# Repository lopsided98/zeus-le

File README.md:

# zeus-le

### Synchronized wireless audio recording system

zeus-le is a system to allow a set of wireless digital audio recorders to maintain sub-sample accurate time synchronization over indefinite periods. A central node broadcasts periodic synchronization packets over Bluetooth LE, which are received by an arbitrary number of recording nodes. The recording nodes use a digital phase-locked loop (PLL) to keep the audio sample clock in sync with the reference. The PLL is implemented using a Kalman filter and linear quadratic regulator.

This repository contains both firmware source code and a custom PCB design for the audio recording hardware. The firmware is written in C for a Nordic nRF53 running Zephyr RTOS. The PCB is designed in KiCad and hosts an nRF53+nRF7002 module, battery charger, SD card, audio ADC and voltage regulators.

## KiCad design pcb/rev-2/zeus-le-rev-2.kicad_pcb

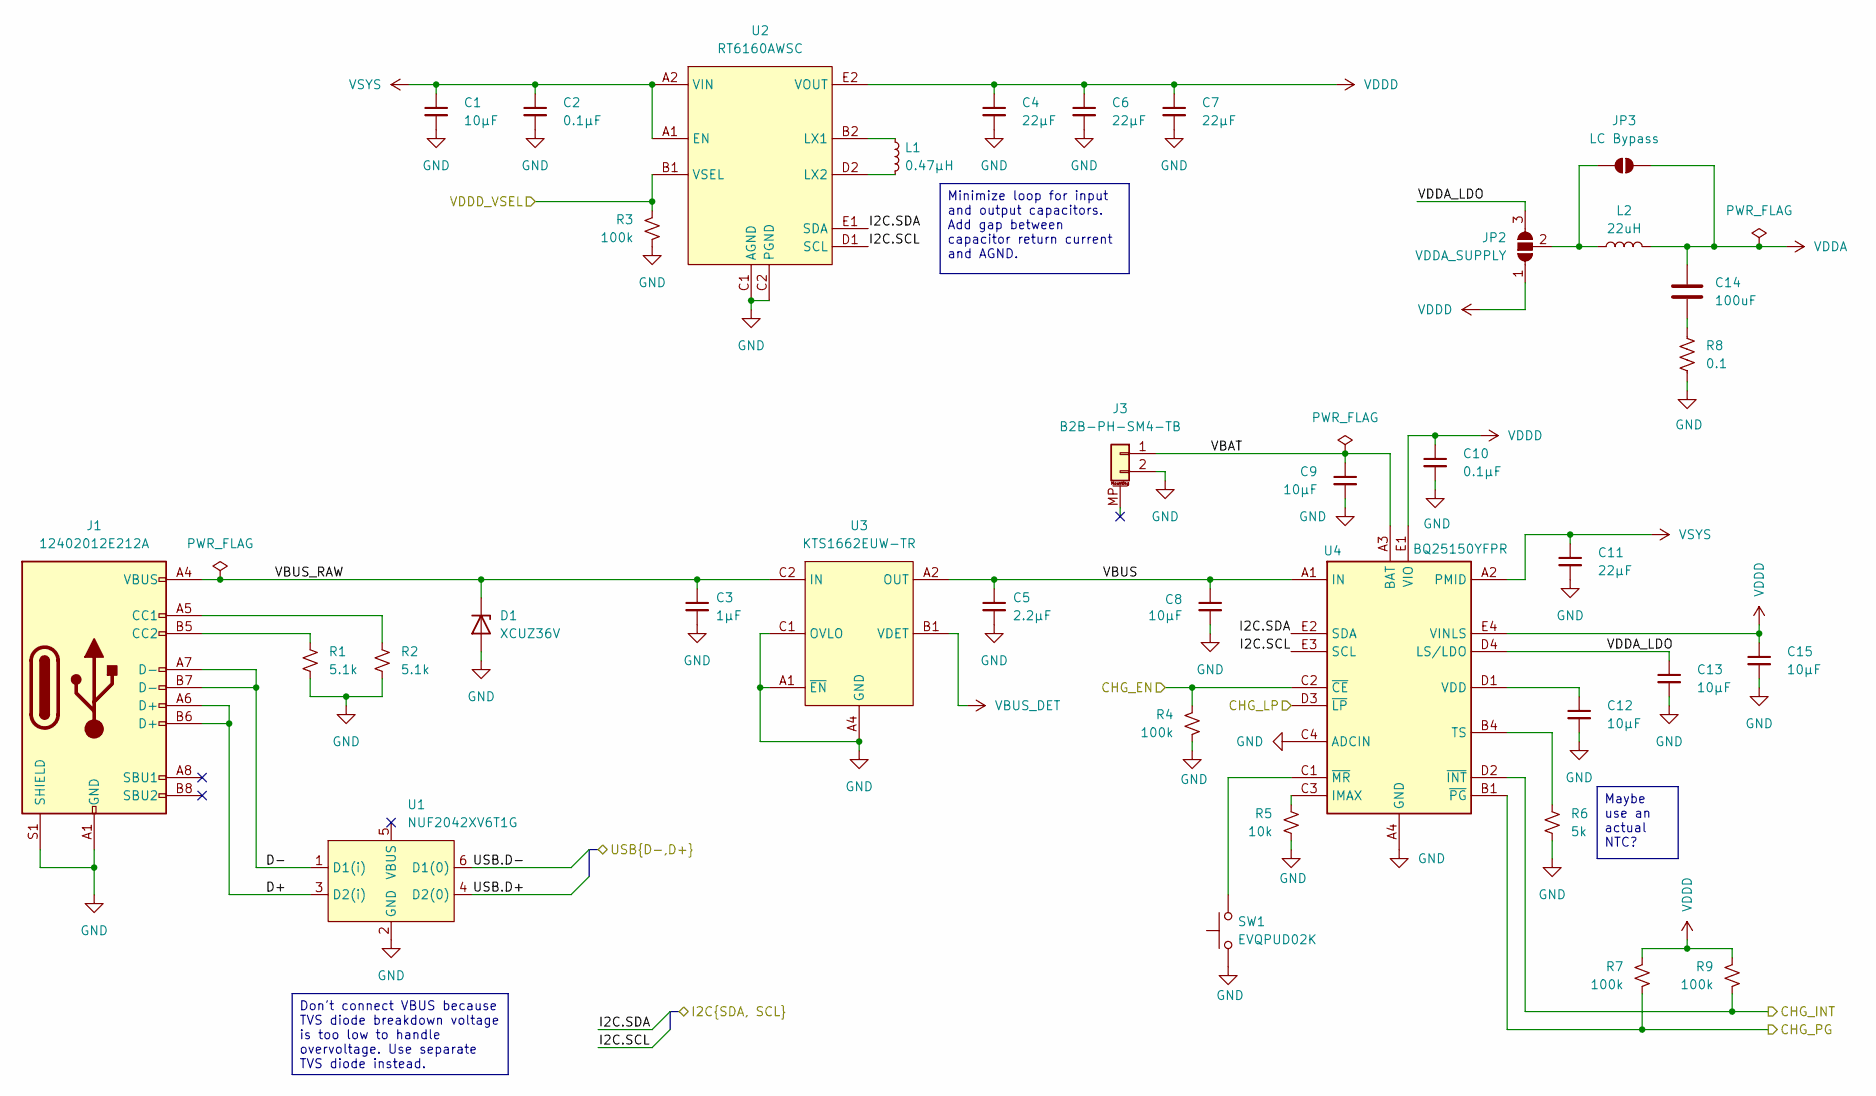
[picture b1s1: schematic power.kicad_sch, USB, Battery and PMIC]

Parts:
C1: 10µF; C_0603_1608Metric
C2, C10: 0.1µF; C_0402_1005Metric_Silkscreen_Clearance
C3: 1µF; C_0603_1608Metric
C4, C6, C7, C11: 22µF; C_0603_1608Metric
C5: 2.2µF; C_0402_1005Metric_Silkscreen_Clearance
C8, C9, C12, C13, C15: 10µF; C_0402_1005Metric_Silkscreen_Clearance
C14: 100uF; C_1206_3216Metric
D1: XCUZ36V; D_SOD-323
J1: 12402012E212A; USB_C_Receptacle_Amphenol_12402012E21-2A
J3: B2B-PH-SM4-TB; JST_PH_B2B-PH-SM4-TB_1x02-1MP_P2.00mm_Vertical; mouser# 306-B2BPHSM4TBLFSN
JP2: VDDA_SUPPLY; SolderJumper-3_P2.0mm_Open_TrianglePad1.0x1.5mm
JP3: LC Bypass; SolderJumper-2_P1.3mm_Open_TrianglePad1.0x1.5mm
L1: 0.47µH; L_Bourns_SRP4020FA_4.1x4.1mm
L2: 22uH; L_0805_2012Metric
R1, R2: 5.1k; R_0402_1005Metric_Silkscreen_Clearance
R3, R4, R7, R9: 100k; R_0402_1005Metric_Silkscreen_Clearance
R5: 10k; R_0402_1005Metric_Silkscreen_Clearance
R6: 5k; R_0402_1005Metric_Silkscreen_Clearance
R8: 0.1; R_0603_1608Metric
SW1: EVQPUD02K; Panasonic_EVQPUM_EVQPUD
U1: NUF2042XV6T1G; SOT-563
U2: RT6160AWSC; Richtek_WLCSP-15_1.4x2.3mm_Layout3x5_P0.4mm_NSMD
U3: KTS1662EUW-TR; Kinetic_WLCSP-12_1.94x1.28mm_Layout4x3_P0.4mm_Ball0.25mm_Pa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
U4: BQ25150YFPR; Texas_DSBGA-20_1.615x2.015mm_Layout4x5_P0.4mm_NSMD

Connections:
/Audio/I2C.SCL: U2.D1 (SCL), U4.E3 (SCL); also elsewhere on the board
/Audio/I2C.SDA: U2.E1 (SDA), U4.E2 (SDA); also elsewhere on the board
/MCU/CHG_EN: R4.1, U4.C2 (~CE); also elsewhere on the board
/MCU/CHG_INT: R9.2, U4.D2 (~INT); also elsewhere on the board
/MCU/CHG_LP: U4.D3 (~LP); also elsewhere on the board
/MCU/CHG_PG: R7.2, U4.B1 (~PG); also elsewhere on the board
/MCU/USB.D+: U1.4 (D2(0)); also elsewhere on the board
/MCU/USB.D-: U1.6 (D1(0)); also elsewhere on the board
/MCU/VDDD_VSEL: R3.1, U2.B1 (VSEL); also elsewhere on the board
/Power/D+: J1.A6 (D+), J1.B6 (D+), U1.3 (D2(i))
/Power/D-: J1.A7 (D-), J1.B7 (D-), U1.1 (D1(i))
/Power/VBAT: C9.1, J3.1, U4.A3 (BAT), U4.B3 (BAT)
/Power/VBUS: C5.1, C8.1, U3.A2 (OUT), U3.A3 (OUT), U3.B2 (OUT), U4.A1 (IN)
/Power/VBUS_RAW: C3.1, D1.1 (K), J1.A4 (VBUS), J1.A9 (VBUS), J1.B4 (VBUS), J1.B9 (VBUS), U3.B3 (IN), U3.C2 (IN), U3.C3 (IN)
/Power/VDDA_LDO: C13.1, JP2.3 (B), U4.D4 (LS/LDO)
GND: C1.2, C2.2, C3.2, C4.2, C5.2, C6.2, C7.2, C8.2, C9.2, C10.2, C11.2, C12.2, C13.2, C15.2, D1.2 (A), J1.A1 (GND), J1.A12 (GND), J1.B1 (GND), J1.B12 (GND), J1.S1 (SHIELD), J3.2, R1.2, R2.2, R3.2, R4.2, R5.2, R6.2, R8.2, SW1.1, U1.2 (GND), U2.C1 (AGND), U2.C2 (PGND), U2.C3 (PGND), U3.A1 (~EN), U3.A4 (GND), U3.B4 (GND), U3.C1 (OVLO), U3.C4 (GND), U4.A4 (GND), U4.C4 (ADCIN); also elsewhere on the board
unnamed: C14.2, R8.1
unnamed: J1.A5 (CC1), R2.1
unnamed: J1.B5 (CC2), R1.1
unnamed: JP2.2 (C), JP3.1 (A), L2.1
unnamed: L1.1, U2.B2 (LX1), U2.B3 (LX1)
unnamed: L1.2, U2.D2 (LX2), U2.D3 (LX2)
unnamed: R5.1, U4.C3 (IMAX)
unnamed: R6.1, U4.B4 (TS)
unnamed: C12.1, U4.D1 (VDD)
unnamed: SW1.2, U4.C1 (~MR)
VBUS_DET: U3.B1 (VDET); also elsewhere on the board
VDDA: C14.1, JP3.2 (B), L2.2; also elsewhere on the board
VDDD: C4.1, C6.1, C7.1, C10.1, C15.1, JP2.1 (A), R7.1, R9.1, U2.E2 (VOUT), U2.E3 (VOUT), U4.E1 (VIO), U4.E4 (VINLS); also elsewhere on the board
VSYS: C1.1, C2.1, C11.1, U2.A1 (EN), U2.A2 (VIN), U2.A3 (VIN), U4.A2 (PMID), U4.B2 (PMID)

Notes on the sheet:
Minimize loop for input and output capacitors. Add gap between capacitor return current and AGND.
Don't connect VBUS because TVS diode breakdown voltage is too low to handle overvoltage. Use separate TVS diode instead.
Maybe use an actual NTC?

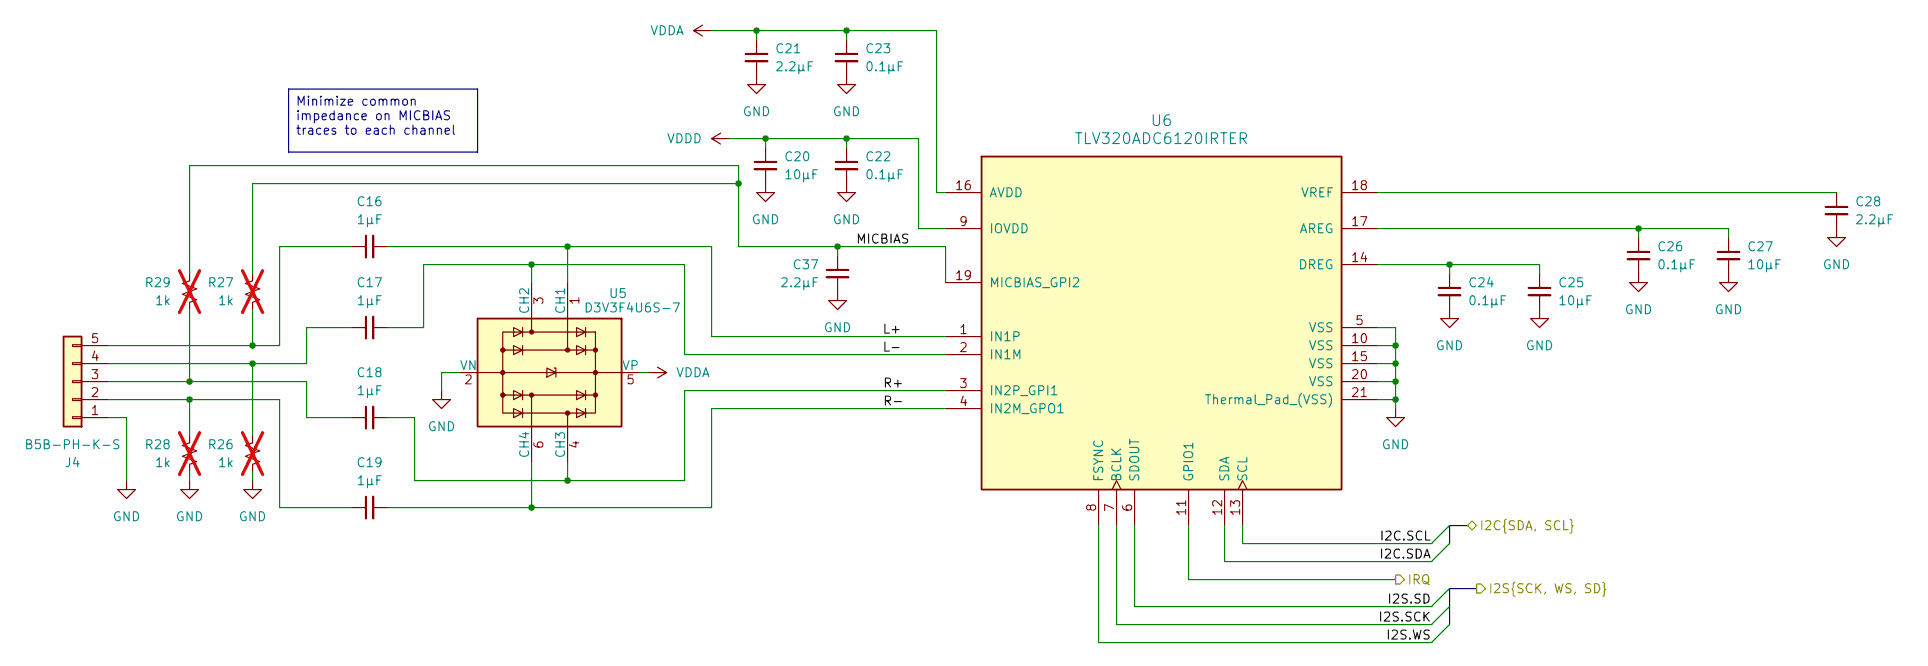
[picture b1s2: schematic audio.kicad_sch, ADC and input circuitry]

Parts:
C16, C17, C18, C19: 1µF; C_1206_3216Metric
C20, C25, C27: 10µF; C_0603_1608Metric
C21, C28, C37: 2.2µF; C_0402_1005Metric_Silkscreen_Clearance
C22, C23, C24, C26: 0.1µF; C_0402_1005Metric_Silkscreen_Clearance
J4: B5B-PH-K-S; JST_PH_B5B-PH-K_1x05_P2.00mm_Vertical
R26, R27, R28, R29: 1k; R_0402_1005Metric_Silkscreen_Clearance; not fitted
U5: D3V3F4U6S-7; SOT-363_SC-70-6
U6: TLV320ADC6120IRTER; Texas_RTE_WQFN-20-1EP_3x3mm_P0.5mm_EP1.4x1.4mm_ThermalVias

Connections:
/Audio/I2C.SCL: U6.13 (SCL); also elsewhere on the board
/Audio/I2C.SDA: U6.12 (SDA); also elsewhere on the board
/Audio/I2S.SCK: U6.7 (BCLK); also elsewhere on the board
/Audio/I2S.SD: U6.6 (SDOUT); also elsewhere on the board
/Audio/I2S.WS: U6.8 (FSYNC); also elsewhere on the board
/Audio/IRQ: U6.11 (GPIO1); also elsewhere on the board
/Audio/L+: C16.2, U5.1 (CH1), U6.1 (IN1P)
/Audio/L-: C17.2, U5.3 (CH2), U6.2 (IN1M)
/Audio/MICBIAS: C37.1, R27.1, R29.1, U6.19 (MICBIAS_GPI2)
/Audio/R+: C18.2, U5.4 (CH3), U6.3 (IN2P_GPI1)
/Audio/R-: C19.2, U5.6 (CH4), U6.4 (IN2M_GPO1)
GND: C20.2, C21.2, C22.2, C23.2, C24.2, C25.2, C26.2, C27.2, C28.2, C37.2, J4.1, R26.2, R28.2, U5.2 (VN), U6.5 (VSS), U6.10 (VSS), U6.15 (VSS), U6.20 (VSS), U6.21 (Thermal_Pad_(VSS)); also elsewhere on the board
unnamed: C19.1, J4.2, R28.1
unnamed: C18.1, J4.3, R29.2
unnamed: C17.1, J4.4, R26.1
unnamed: C16.1, J4.5, R27.2
unnamed: C26.1, C27.1, U6.17 (AREG)
unnamed: C24.1, C25.1, U6.14 (DREG)
unnamed: C28.1, U6.18 (VREF)
VDDA: C21.1, C23.1, U5.5 (VP), U6.16 (AVDD); also elsewhere on the board
VDDD: C20.1, C22.1, U6.9 (IOVDD); also elsewhere on the board

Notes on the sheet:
Minimize common impedance on MICBIAS traces to each channel

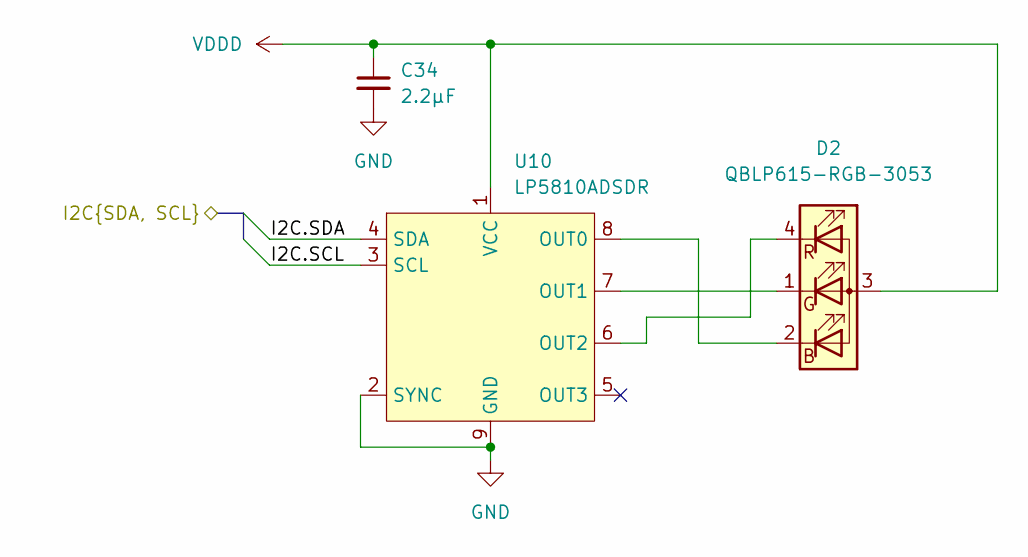
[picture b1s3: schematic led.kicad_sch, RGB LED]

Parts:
C34: 2.2µF; C_0402_1005Metric_Silkscreen_Clearance
D2: QBLP615-RGB-3053; LED_QBLP615-RGB-3053
U10: LP5810ADSDR; WSON-8-1EP_3x3mm_P0.65mm_EP1.65x2.4mm_ThermalVias

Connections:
/Audio/I2C.SCL: U10.3 (SCL); also elsewhere on the board
/Audio/I2C.SDA: U10.4 (SDA); also elsewhere on the board
GND: C34.2, U10.2 (SYNC), U10.9 (GND); also elsewhere on the board
unnamed: D2.2 (BK), U10.8 (OUT0)
unnamed: D2.1 (GK), U10.7 (OUT1)
unnamed: D2.4 (RK), U10.6 (OUT2)
VDDD: C34.1, D2.3 (A), U10.1 (VCC); also elsewhere on the board

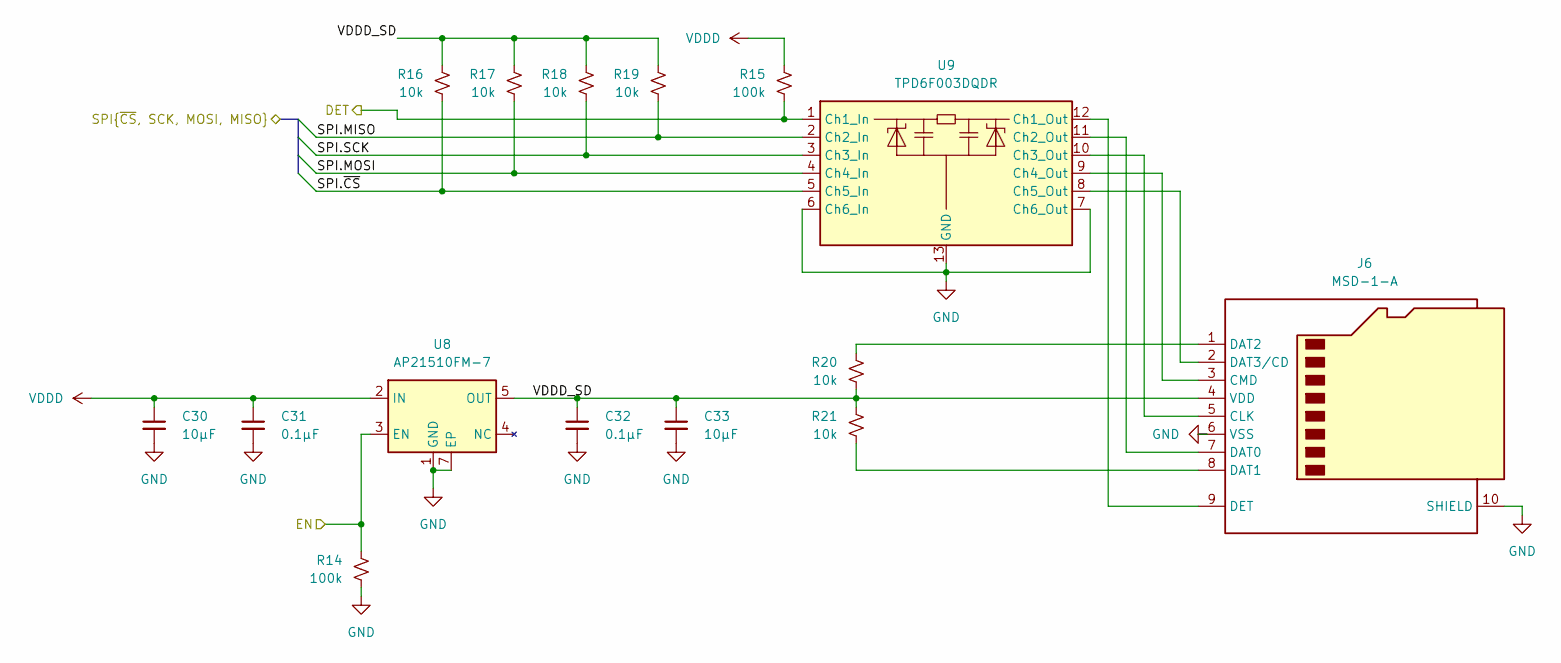
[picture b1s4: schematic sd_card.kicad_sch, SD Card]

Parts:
C30, C33: 10µF; C_0603_1608Metric
C31, C32: 0.1µF; C_0402_1005Metric_Silkscreen_Clearance
J6: MSD-1-A; microSD_HC_CUI_MSD-1-A
R14, R15: 100k; R_0402_1005Metric_Silkscreen_Clearance
R16, R17, R18, R19, R20, R21: 10k; R_0402_1005Metric_Silkscreen_Clearance
U8: AP21510FM-7; Diodes_UDFN2018-6
U9: TPD6F003DQDR; Texas_R-PWSON-N12_EP0.4x2mm; digikey# 296-25802-1-ND

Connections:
/MCU/SD.MISO: R19.2, U9.2 (Ch2_In); also elsewhere on the board
/MCU/SD.MOSI: R17.2, U9.4 (Ch4_In); also elsewhere on the board
/MCU/SD.SCK: R18.2, U9.3 (Ch3_In); also elsewhere on the board
/MCU/SD.~CS: R16.2, U9.5 (Ch5_In); also elsewhere on the board
/MCU/SD_DET: R15.2, U9.1 (Ch1_In); also elsewhere on the board
/MCU/SD_EN: R14.1, U8.3 (EN); also elsewhere on the board
/SD Card/VDDD_SD: C32.1, C33.1, J6.4 (VDD), R16.1, R17.1, R18.1, R19.1, R20.2, R21.1, U8.5 (OUT), U8.6 (OUT)
GND: C30.2, C31.2, C32.2, C33.2, J6.6 (VSS), J6.10 (SHIELD), R14.2, U8.1 (GND), U8.7 (EP), U9.6 (Ch6_In), U9.7 (Ch6_Out), U9.13 (GND); also elsewhere on the board
unnamed: J6.5 (CLK), U9.10 (Ch3_Out)
unnamed: J6.3 (CMD), U9.9 (Ch4_Out)
unnamed: J6.7 (DAT0), U9.11 (Ch2_Out)
unnamed: J6.8 (DAT1), R21.2
unnamed: J6.1 (DAT2), R20.1
unnamed: J6.2 (DAT3/CD), U9.8 (Ch5_Out)
unnamed: J6.9 (DET), U9.12 (Ch1_Out)
VDDD: C30.1, C31.1, R15.1, U8.2 (IN); also elsewhere on the board

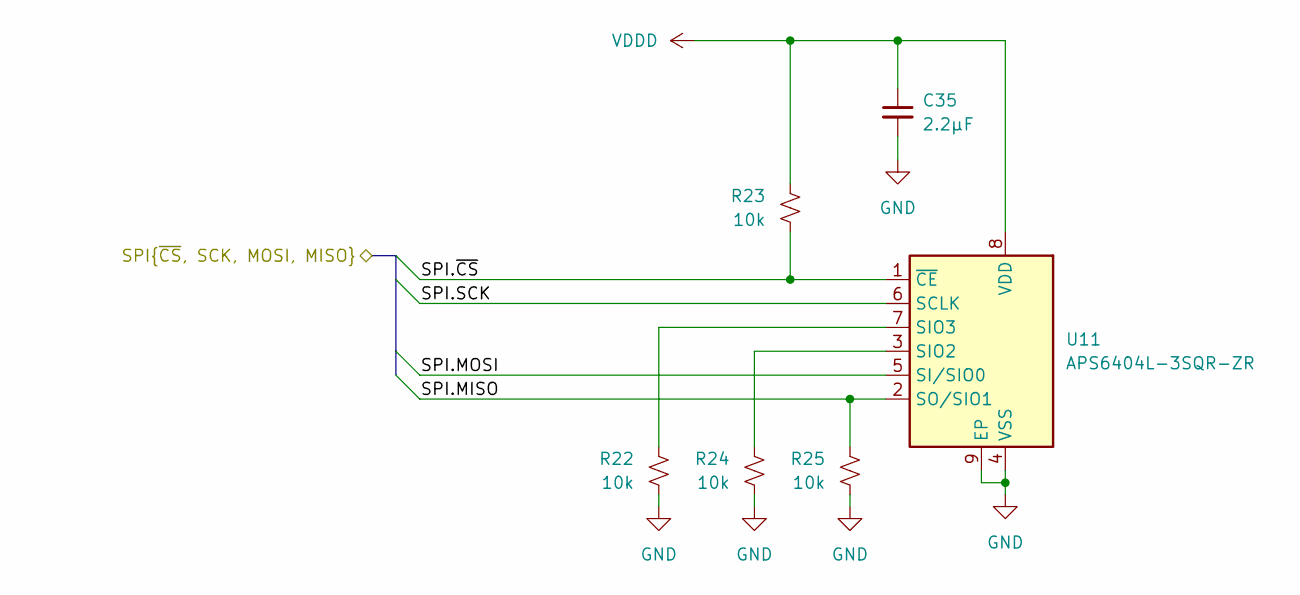
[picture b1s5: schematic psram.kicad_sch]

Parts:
C35: 2.2µF; C_0402_1005Metric_Silkscreen_Clearance
R22, R23, R24, R25: 10k; R_0402_1005Metric_Silkscreen_Clearance
U11: APS6404L-3SQR-ZR; Winbond_USON-8-1EP_3x2mm_P0.5mm_EP0.2x1.6mm

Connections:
/MCU/RAM.MISO: R25.1, U11.2 (SO/SIO1); also elsewhere on the board
/MCU/RAM.MOSI: U11.5 (SI/SIO0); also elsewhere on the board
/MCU/RAM.SCK: U11.6 (SCLK); also elsewhere on the board
/MCU/RAM.~CS: R23.2, U11.1 (~CE); also elsewhere on the board
GND: C35.2, R22.2, R24.2, R25.2, U11.4 (VSS), U11.9 (EP); also elsewhere on the board
unnamed: R24.1, U11.3 (SIO2)
unnamed: R22.1, U11.7 (SIO3)
VDDD: C35.1, R23.1, U11.8 (VDD); also elsewhere on the board

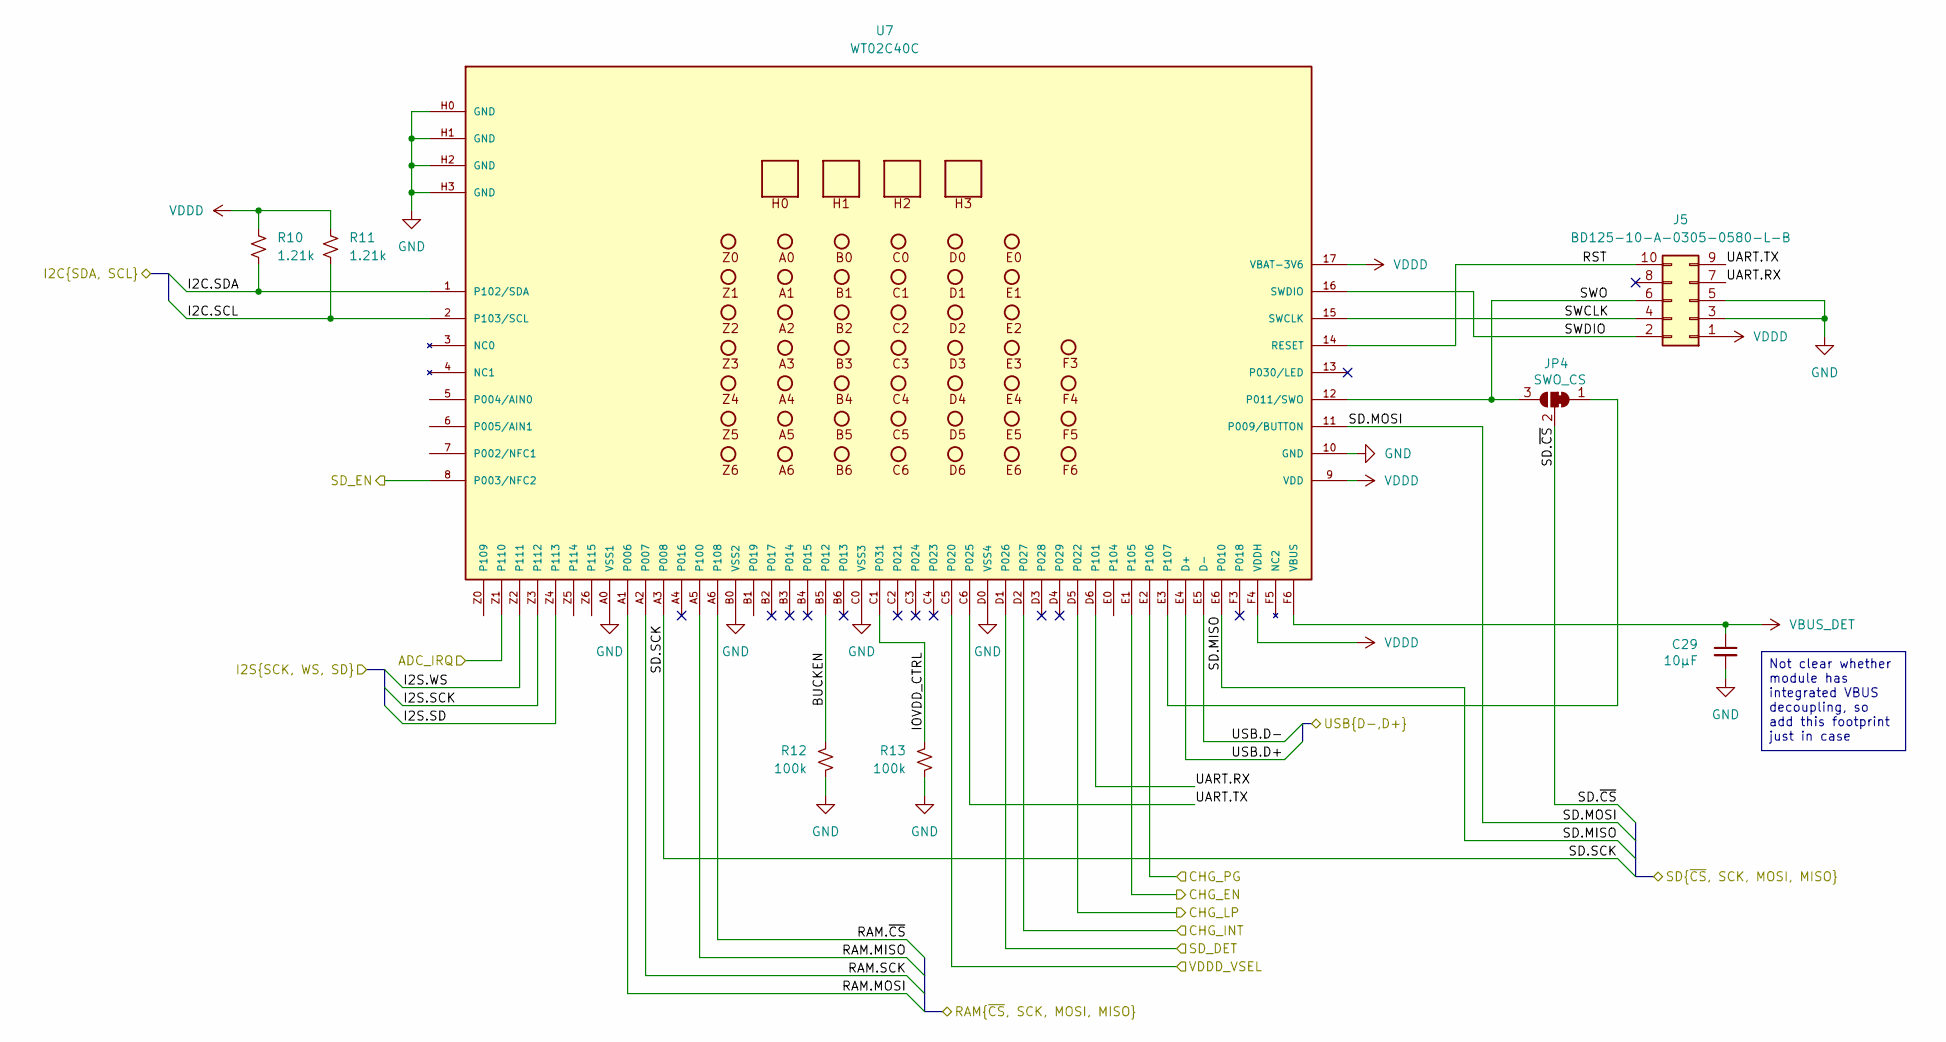
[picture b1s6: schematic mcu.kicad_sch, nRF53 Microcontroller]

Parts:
C29: 10µF; C_0402_1005Metric_Silkscreen_Clearance
J5: BD125-10-A-0305-0580-L-B; PinHeader_2x05_P1.27mm_Vertical_SMD
JP4: SWO_CS; SolderJumper-3_P2.0mm_Open_TrianglePad1.0x1.5mm
R10, R11: 1.21k; R_0402_1005Metric_Silkscreen_Clearance
R12, R13: 100k; R_0402_1005Metric_Silkscreen_Clearance
U7: WT02C40C; WT02C40C-VC; digikey# 1914-WT02C40CCT-ND

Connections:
/Audio/I2C.SCL: R11.2, U7.2 (P103/SCL); also elsewhere on the board
/Audio/I2C.SDA: R10.2, U7.1 (P102/SDA); also elsewhere on the board
/Audio/I2S.SCK: U7.Z3 (P112); also elsewhere on the board
/Audio/I2S.SD: U7.Z4 (P113); also elsewhere on the board
/Audio/I2S.WS: U7.Z2 (P111); also elsewhere on the board
/Audio/IRQ: U7.Z1 (P110); also elsewhere on the board
/MCU/BUCKEN: R12.1, U7.B5 (P012)
/MCU/CHG_EN: U7.E1 (P105); also elsewhere on the board
/MCU/CHG_INT: U7.D2 (P027); also elsewhere on the board
/MCU/CHG_LP: U7.D5 (P022); also elsewhere on the board
/MCU/CHG_PG: U7.E2 (P106); also elsewhere on the board
/MCU/IOVDD_CTRL: R13.1, U7.C1 (P031)
/MCU/RAM.MISO: U7.A5 (P100); also elsewhere on the board
/MCU/RAM.MOSI: U7.A1 (P006); also elsewhere on the board
/MCU/RAM.SCK: U7.A2 (P007); also elsewhere on the board
/MCU/RAM.~CS: U7.A6 (P108); also elsewhere on the board
/MCU/RST: J5.10, U7.14 (RESET)
/MCU/SD.MISO: U7.E6 (P010); also elsewhere on the board
/MCU/SD.MOSI: U7.11 (P009/BUTTON); also elsewhere on the board
/MCU/SD.SCK: U7.A3 (P008); also elsewhere on the board
/MCU/SD.~CS: JP4.2 (C); also elsewhere on the board
/MCU/SD_DET: U7.D1 (P026); also elsewhere on the board
/MCU/SD_EN: U7.8 (P003/NFC2); also elsewhere on the board
/MCU/SWCLK: J5.4, U7.15 (SWCLK)
/MCU/SWDIO: J5.2, U7.16 (SWDIO)
/MCU/SWO: J5.6, JP4.3 (B), U7.12 (P011/SWO)
/MCU/UART.RX: J5.7, U7.D6 (P101)
/MCU/UART.TX: J5.9, U7.C6 (P025)
/MCU/USB.D+: U7.E4 (D+); also elsewhere on the board
/MCU/USB.D-: U7.E5 (D-); also elsewhere on the board
/MCU/VDDD_VSEL: U7.C5 (P020); also elsewhere on the board
GND: C29.2, J5.3, J5.5, R12.2, R13.2, U7.10 (GND), U7.A0 (VSS1), U7.B0 (VSS2), U7.C0 (VSS3), U7.D0 (VSS4), U7.H0 (GND), U7.H1 (GND), U7.H2 (GND), U7.H3 (GND); also elsewhere on the board
unnamed: JP4.1 (A), U7.E3 (P107)
VBUS_DET: C29.1, U7.F6 (VBUS); also elsewhere on the board
VDDD: J5.1, R10.1, R11.1, U7.9 (VDD), U7.17 (VBAT-3V6), U7.F4 (VDDH); also elsewhere on the board

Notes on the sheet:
Not clear whether module has integrated VBUS decoupling, so add this footprint just in case

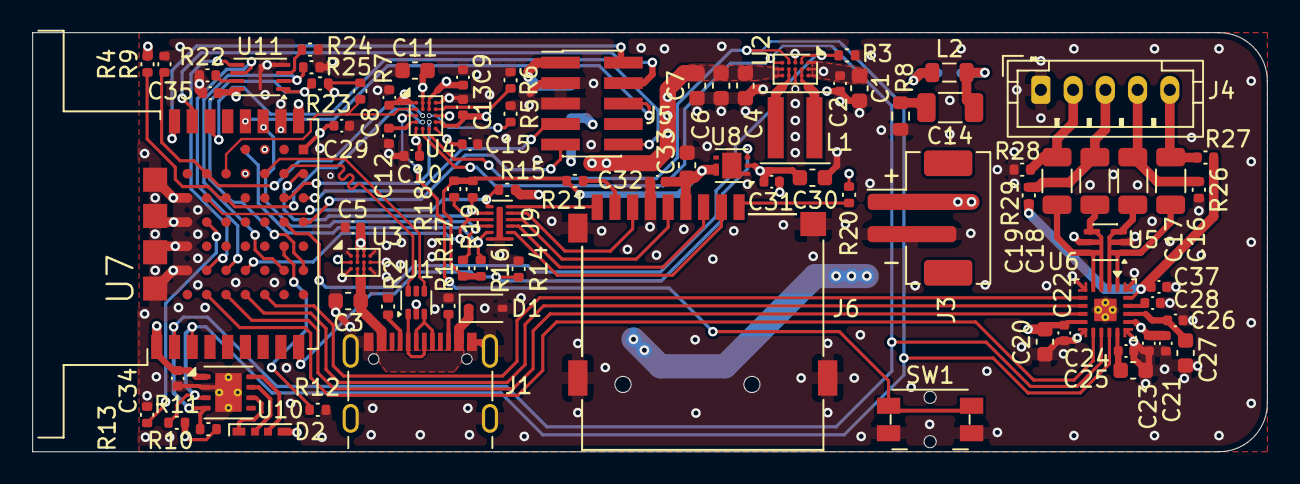
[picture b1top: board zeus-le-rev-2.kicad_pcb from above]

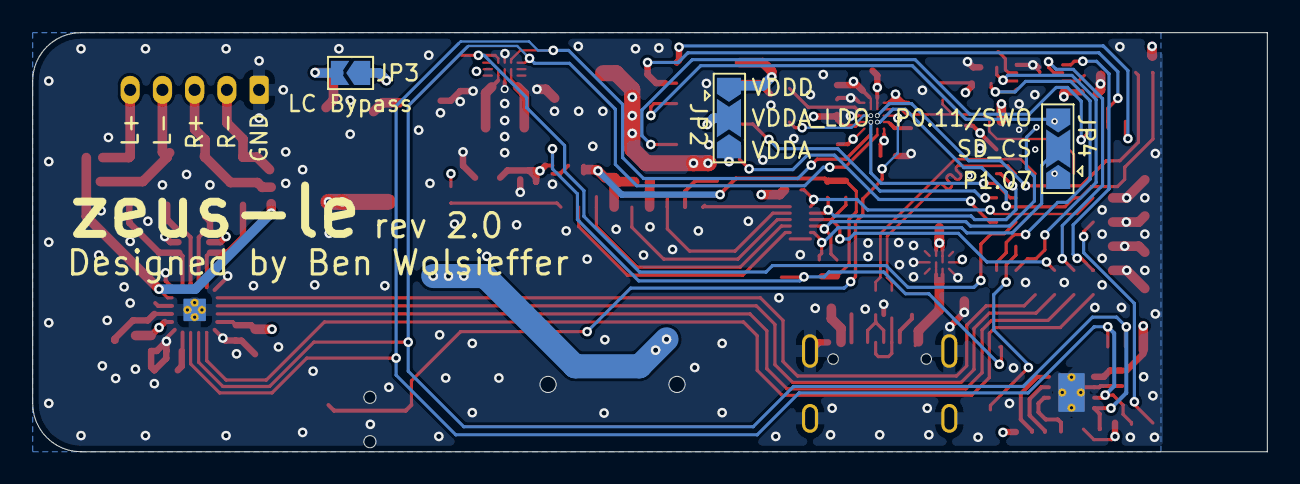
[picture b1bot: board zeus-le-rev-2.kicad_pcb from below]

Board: 6 copper layers, 76.6 x 26.0 mm, 89 parts (3 on the bottom side), 78 nets.

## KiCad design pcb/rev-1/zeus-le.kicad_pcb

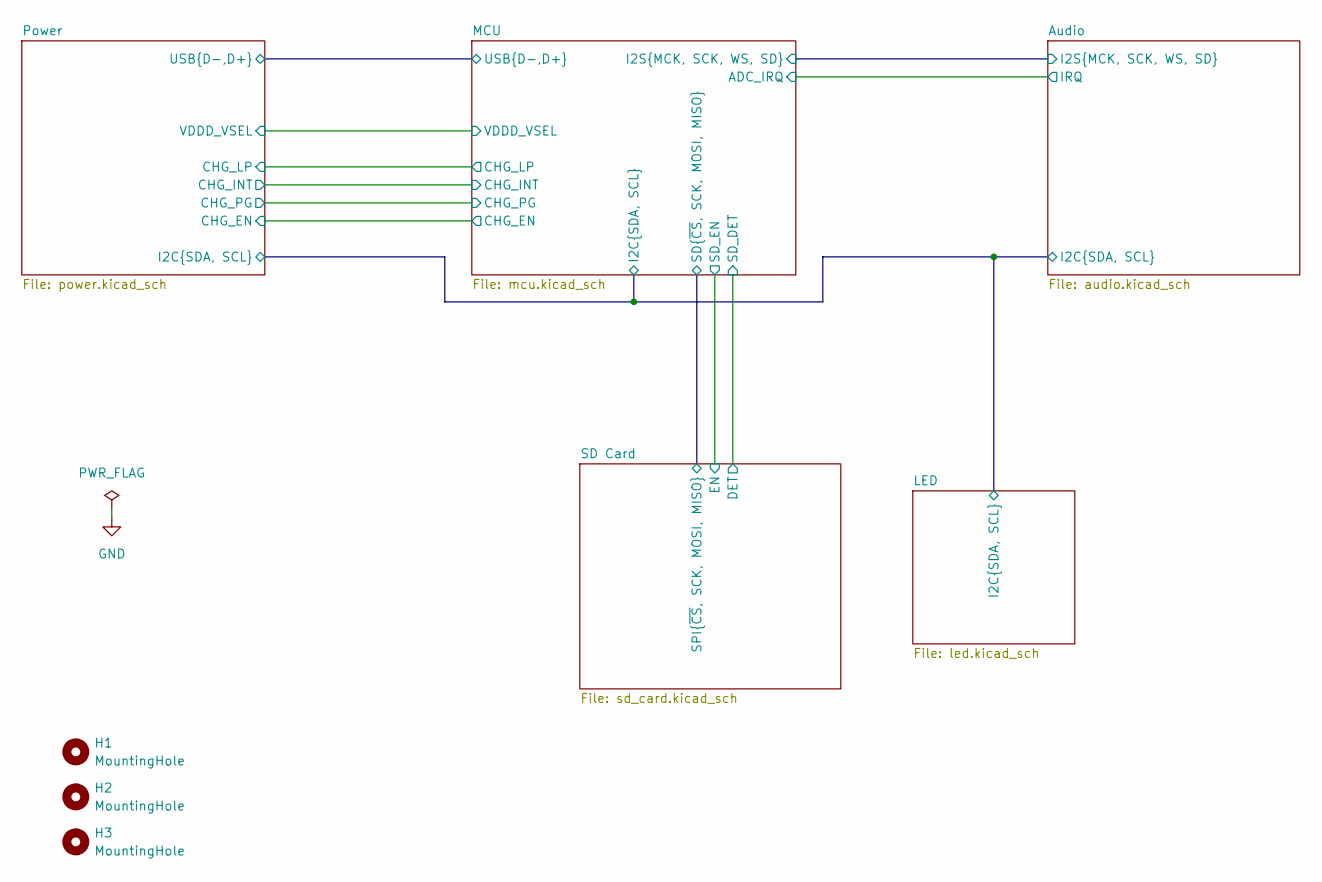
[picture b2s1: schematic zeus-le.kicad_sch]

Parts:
H1, H2, H3: MountingHole; MountingHole_2.2mm_M2

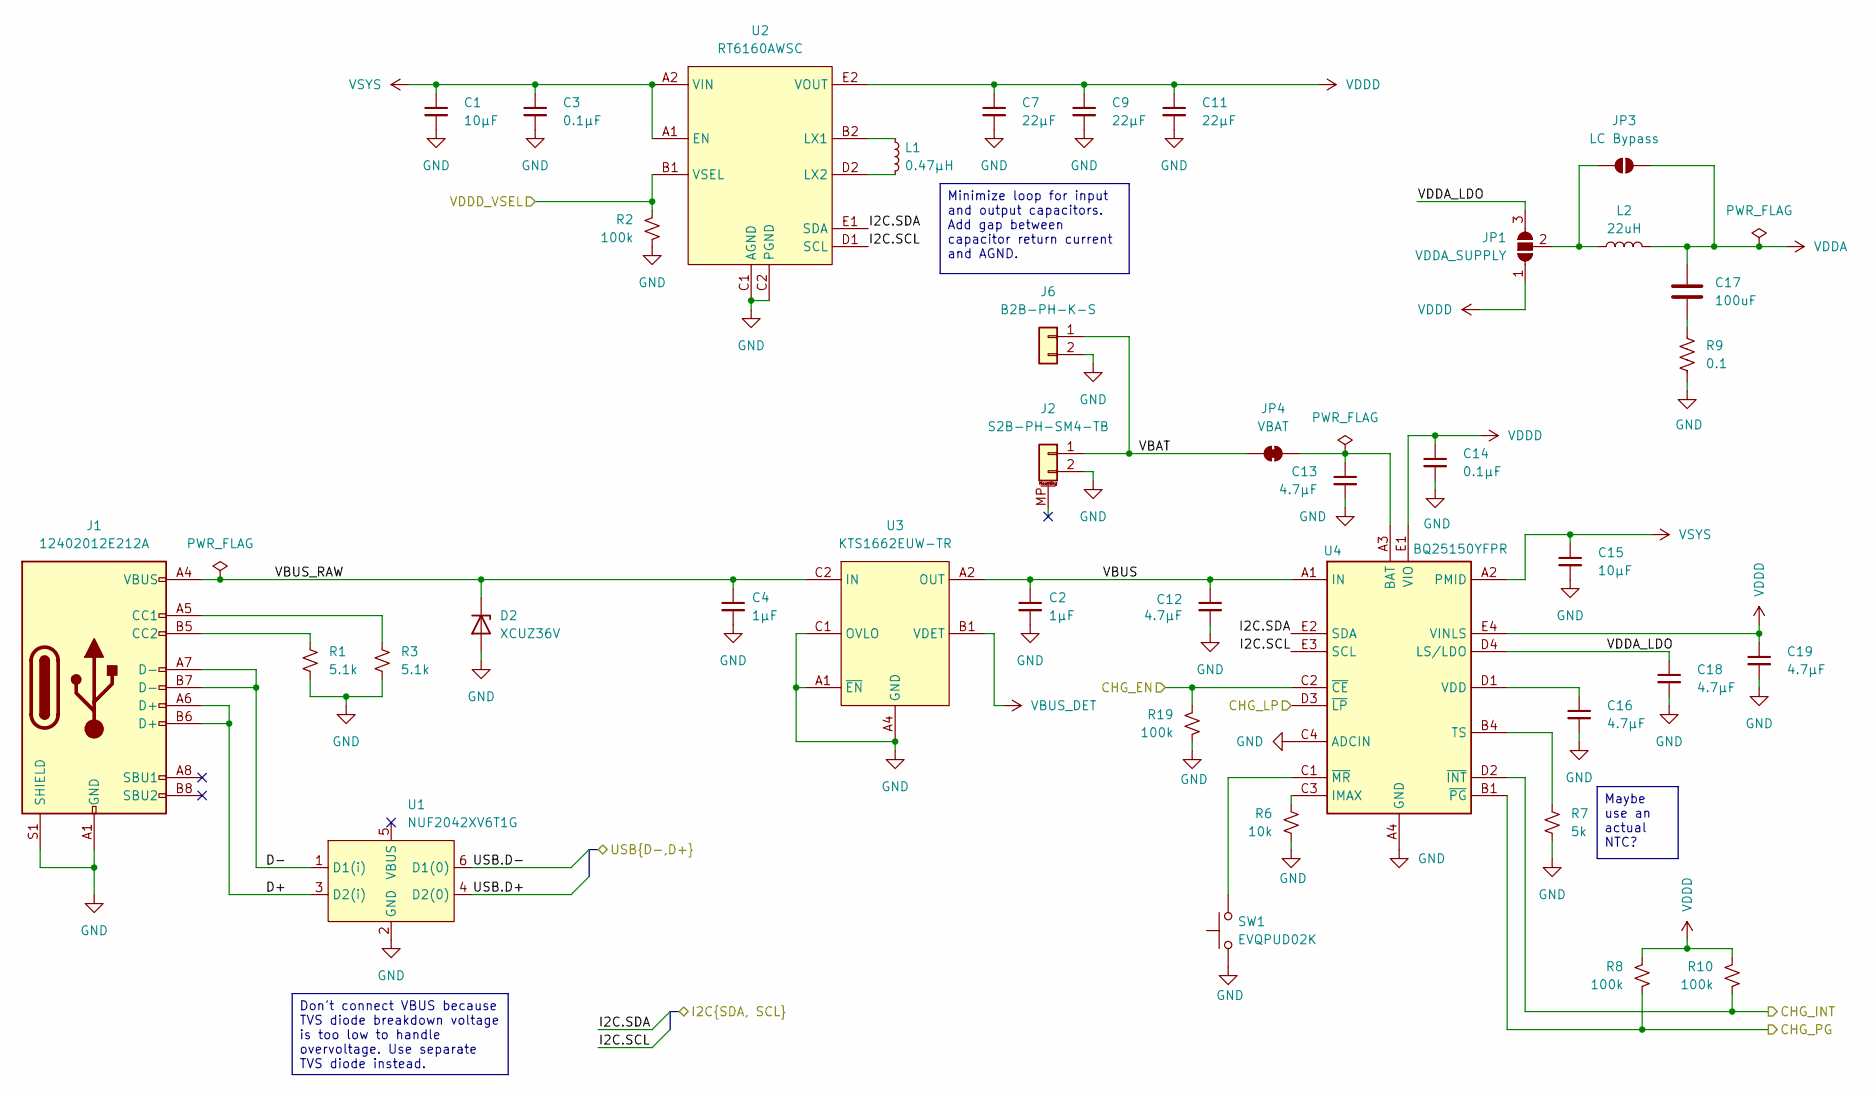
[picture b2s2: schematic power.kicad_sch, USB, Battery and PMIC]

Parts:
C1, C15: 10µF; C_0603_1608Metric
C2, C4: 1µF; C_0603_1608Metric
C3, C14: 0.1µF; C_0402_1005Metric
C7, C9, C11: 22µF; C_0603_1608Metric
C12, C13, C16, C18, C19: 4.7µF; C_0603_1608Metric
C17: 100uF; C_1206_3216Metric
D2: XCUZ36V; D_SOD-323
J1: 12402012E212A; USB_C_Receptacle_Amphenol_12402012E21-2A
J2: S2B-PH-SM4-TB; JST_PH_S2B-PH-SM4-TB_1x02-1MP_P2.00mm_Horizontal
J6: B2B-PH-K-S; JST_PH_B2B-PH-K_1x02_P2.00mm_Vertical
JP1: VDDA_SUPPLY; SolderJumper-3_P2.0mm_Open_TrianglePad1.0x1.5mm
JP3: LC Bypass; SolderJumper-2_P1.3mm_Open_TrianglePad1.0x1.5mm
JP4: VBAT; SolderJumper-2_P1.3mm_Bridged_RoundedPad1.0x1.5mm
L1: 0.47µH; L_Bourns_SRP4020FA_4.1x4.1mm
L2: 22uH; L_0805_2012Metric
R1, R3: 5.1k; R_0402_1005Metric
R2, R8, R10, R19: 100k; R_0402_1005Metric
R6: 10k; R_0402_1005Metric
R7: 5k; R_0402_1005Metric
R9: 0.1; R_0603_1608Metric
SW1: EVQPUD02K; Panasonic_EVQPUM_EVQPUD
U1: NUF2042XV6T1G; SOT-563
U2: RT6160AWSC; Richtek_WLCSP-15_1.4x2.3mm_Layout3x5_P0.4mm_NSMD
U3: KTS1662EUW-TR; Kinetic_WLCSP-12_1.94x1.28mm_Layout4x3_P0.4mm_Ball0.25mm_Pa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
U4: BQ25150YFPR; Texas_DSBGA-20_1.615x2.015mm_Layout4x5_P0.4mm_NSMD

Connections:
/Audio/I2C.SCL: U2.D1 (SCL), U4.E3 (SCL); also elsewhere on the board
/Audio/I2C.SDA: U2.E1 (SDA), U4.E2 (SDA); also elsewhere on the board
/MCU/CHG_EN: R19.1, U4.C2 (~CE); also elsewhere on the board
/MCU/CHG_INT: R10.2, U4.D2 (~INT); also elsewhere on the board
/MCU/CHG_LP: U4.D3 (~LP); also elsewhere on the board
/MCU/CHG_PG: R8.2, U4.B1 (~PG); also elsewhere on the board
/MCU/USB.D+: U1.4 (D2(0)); also elsewhere on the board
/MCU/USB.D-: U1.6 (D1(0)); also elsewhere on the board
/MCU/VDDD_VSEL: R2.1, U2.B1 (VSEL); also elsewhere on the board
/Power/D+: J1.A6 (D+), J1.B6 (D+), U1.3 (D2(i))
/Power/D-: J1.A7 (D-), J1.B7 (D-), U1.1 (D1(i))
/Power/VBAT: J2.1, J6.1, JP4.1 (A)
/Power/VBUS: C2.1, C12.1, U3.A2 (OUT), U3.A3 (OUT), U3.B2 (OUT), U4.A1 (IN)
/Power/VBUS_RAW: C4.1, D2.1 (K), J1.A4 (VBUS), J1.A9 (VBUS), J1.B4 (VBUS), J1.B9 (VBUS), U3.B3 (IN), U3.C2 (IN), U3.C3 (IN)
/Power/VDDA_LDO: C18.1, JP1.3 (B), U4.D4 (LS/LDO)
GND: C1.2, C2.2, C3.2, C4.2, C7.2, C9.2, C11.2, C12.2, C13.2, C14.2, C15.2, C16.2, C18.2, C19.2, D2.2 (A), J1.A1 (GND), J1.A12 (GND), J1.B1 (GND), J1.B12 (GND), J1.S1 (SHIELD), J2.2, J6.2, R1.2, R2.2, R3.2, R6.2, R7.2, R9.2, R19.2, SW1.1, U1.2 (GND), U2.C1 (AGND), U2.C2 (PGND), U2.C3 (PGND), U3.A1 (~EN), U3.A4 (GND), U3.B4 (GND), U3.C1 (OVLO), U3.C4 (GND), U4.A4 (GND), U4.C4 (ADCIN); also elsewhere on the board
unnamed: C17.2, R9.1
unnamed: J1.A5 (CC1), R3.1
unnamed: J1.B5 (CC2), R1.1
unnamed: JP1.2 (C), JP3.1 (A), L2.1
unnamed: C13.1, JP4.2 (B), U4.A3 (BAT), U4.B3 (BAT)
unnamed: L1.1, U2.B2 (LX1), U2.B3 (LX1)
unnamed: L1.2, U2.D2 (LX2), U2.D3 (LX2)
unnamed: R6.1, U4.C3 (IMAX)
unnamed: R7.1, U4.B4 (TS)
unnamed: C16.1, U4.D1 (VDD)
unnamed: SW1.2, U4.C1 (~MR)
VBUS_DET: U3.B1 (VDET); also elsewhere on the board
VDDA: C17.1, JP3.2 (B), L2.2; also elsewhere on the board
VDDD: C7.1, C9.1, C11.1, C14.1, C19.1, JP1.1 (A), R8.1, R10.1, U2.E2 (VOUT), U2.E3 (VOUT), U4.E1 (VIO), U4.E4 (VINLS); also elsewhere on the board
VSYS: C1.1, C3.1, C15.1, U2.A1 (EN), U2.A2 (VIN), U2.A3 (VIN), U4.A2 (PMID), U4.B2 (PMID)

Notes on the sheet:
Minimize loop for input and output capacitors. Add gap between capacitor return current and AGND.
Don't connect VBUS because TVS diode breakdown voltage is too low to handle overvoltage. Use separate TVS diode instead.
Maybe use an actual NTC?

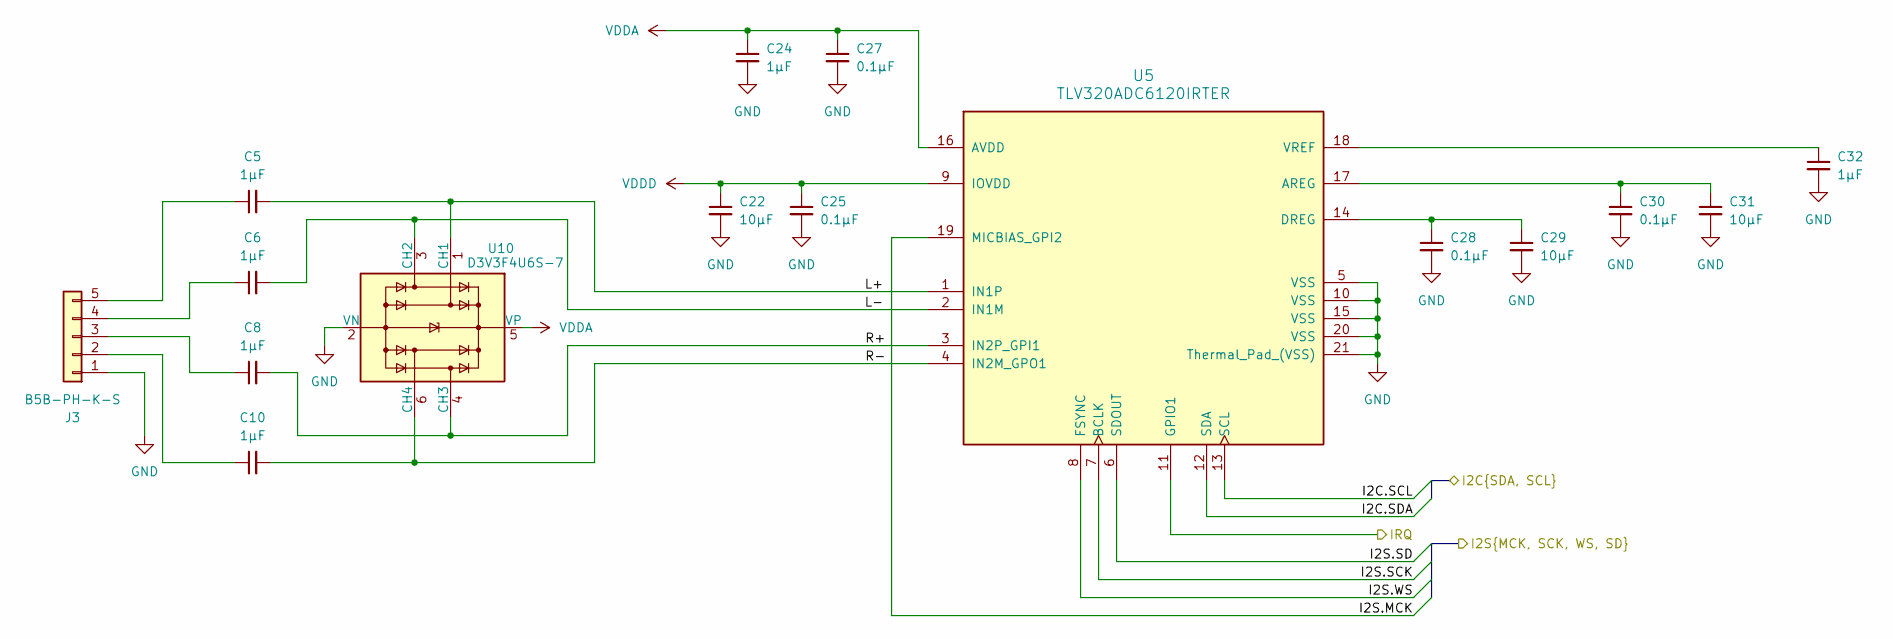
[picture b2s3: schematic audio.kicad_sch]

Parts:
C5, C6, C8, C10: 1µF; C_1206_3216Metric
C22, C29, C31: 10µF; C_0603_1608Metric
C24, C32: 1µF; C_0603_1608Metric
C25, C27, C28, C30: 0.1µF; C_0402_1005Metric
J3: B5B-PH-K-S; JST_PH_B5B-PH-K_1x05_P2.00mm_Vertical
U5: TLV320ADC6120IRTER; Texas_RTE_WQFN-20-1EP_3x3mm_P0.5mm_EP1.4x1.4mm_ThermalVias
U10: D3V3F4U6S-7; SOT-363_SC-70-6

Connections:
/Audio/I2C.SCL: U5.13 (SCL); also elsewhere on the board
/Audio/I2C.SDA: U5.12 (SDA); also elsewhere on the board
/Audio/I2S.MCK: U5.19 (MICBIAS_GPI2); also elsewhere on the board
/Audio/I2S.SCK: U5.7 (BCLK); also elsewhere on the board
/Audio/I2S.SD: U5.6 (SDOUT); also elsewhere on the board
/Audio/I2S.WS: U5.8 (FSYNC); also elsewhere on the board
/Audio/IRQ: U5.11 (GPIO1); also elsewhere on the board
/Audio/L+: C5.2, U5.1 (IN1P), U10.1 (CH1)
/Audio/L-: C6.2, U5.2 (IN1M), U10.3 (CH2)
/Audio/R+: C8.2, U5.3 (IN2P_GPI1), U10.4 (CH3)
/Audio/R-: C10.2, U5.4 (IN2M_GPO1), U10.6 (CH4)
GND: C22.2, C24.2, C25.2, C27.2, C28.2, C29.2, C30.2, C31.2, C32.2, J3.1, U5.5 (VSS), U5.10 (VSS), U5.15 (VSS), U5.20 (VSS), U5.21 (Thermal_Pad_(VSS)), U10.2 (VN); also elsewhere on the board
unnamed: C10.1, J3.2
unnamed: C8.1, J3.3
unnamed: C6.1, J3.4
unnamed: C5.1, J3.5
unnamed: C30.1, C31.1, U5.17 (AREG)
unnamed: C28.1, C29.1, U5.14 (DREG)
unnamed: C32.1, U5.18 (VREF)
VDDA: C24.1, C27.1, U5.16 (AVDD), U10.5 (VP); also elsewhere on the board
VDDD: C22.1, C25.1, U5.9 (IOVDD); also elsewhere on the board
